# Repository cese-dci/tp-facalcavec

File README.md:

# Cargador modular de baterías industriales con acceso remoto

Repositorio perteneciente a la materia Diseño de circuitos impresos del CESE - 2021.

En el se encontrará el diseño del esquemático y PCB del TP final de la carrera.

&nbsp;

## Consideraciones de diseño del PCB

Se detallan a continuación los considerandos a tener en cuenta en el diseño y construcción del circuito impreso del cargador modular de baterías industriales.

### Dimensiones y ubicación
La placa debe adaptarse a un gabinete ya existente, por lo tanto sus medidas no deben superar los siguientes límites

Largo máximo      : 200 mm  
Ancho máximo      : 100 mm  

### Coordenadas de los agujero de montaje ( vista la placa de frente )

Agujero inferior izquierdo  : ( 0 mm, 0 mm )  
Agujero inferior derecho    : ( 184 mm, 0 mm )  
Agujero superior izquierdo  : ( 0 mm, -86 mm )  
Agujero superior derecho    : ( 184 mm, -86 mm )  

### Coordenadas del Display gráfico respecto del agujero inferior izquierdo

Ángulo inferior izquierdo   : ( 16 mm, -18.5 mm )  
Ángulo inferior derecho     : ( 102.5 mm, -18.5 mm )  
Ángulo superior izquierdo   : ( 16 mm, -72 mm )  
Ángulo superior derecho     : ( 102.5 mm, -72 mm )  

### Coordenadas del teclado respecto del agujero inferior izquierdo  
Centro botón 1    : ( 21 mm, -2 mm )  
Centro botón 2    : ( 46.7 mm, -2 mm )  
Centro botón 3    : ( 72 mm, -2 mm )  
Centro botón 4    : ( 997.5 mm, -2 mm )  

### Estándares de fabricación
Debido a la poca densidad de conexiones entre componentes el diseño se realizará en doble faz ( dos capas ).
&nbsp;
De acuerdo a la documentación aportada por el fabricantede PCB Mayer se implementará la tecnología “8MILS” donde  
&nbsp;
Diámetro de agujero: 16 mils / 0.40 mm  
Diámetro de pad o vía: 32 mils / 0.8 mm  
Ancho de traza: 8 mils / 0.20 mm  
Separación entre trazas: 7 mils / 0.18 mm  
Separación entre traza y pad: 6 mils / 0.15 mm  
Distancia de cobre a borde: 12 mils / 0.30 mm  
Altura - trazo de letras: 30 - 5  

### Componentes a utilizar  
Para el diseño de la placa se utilizarán componentes SMD para las resistencias, capacitores cerámicos y algunos circuitos integrados, mientras que el resto serán del tipo insertados (THT).  
Este criterio se debe a que la mayoría de los componentes que integran la placa se quieren adquirir en el mercado local.  
Para aprovechar el espacio disponible se colocaran componentes SMD en las dos caras del PCB.

### Método de armado
El tipo de armado y soldado de la placa se pretende hacer de forma manual

------------------------------------------------------------------------

&nbsp;

&nbsp;

<br />This work is licensed under a <a rel="license" href="http://creativecommons.org/licenses/by-nc-sa/4.0/">Creative Commons Attribution-NonCommercial-ShareAlike 4.0 International License</a>.

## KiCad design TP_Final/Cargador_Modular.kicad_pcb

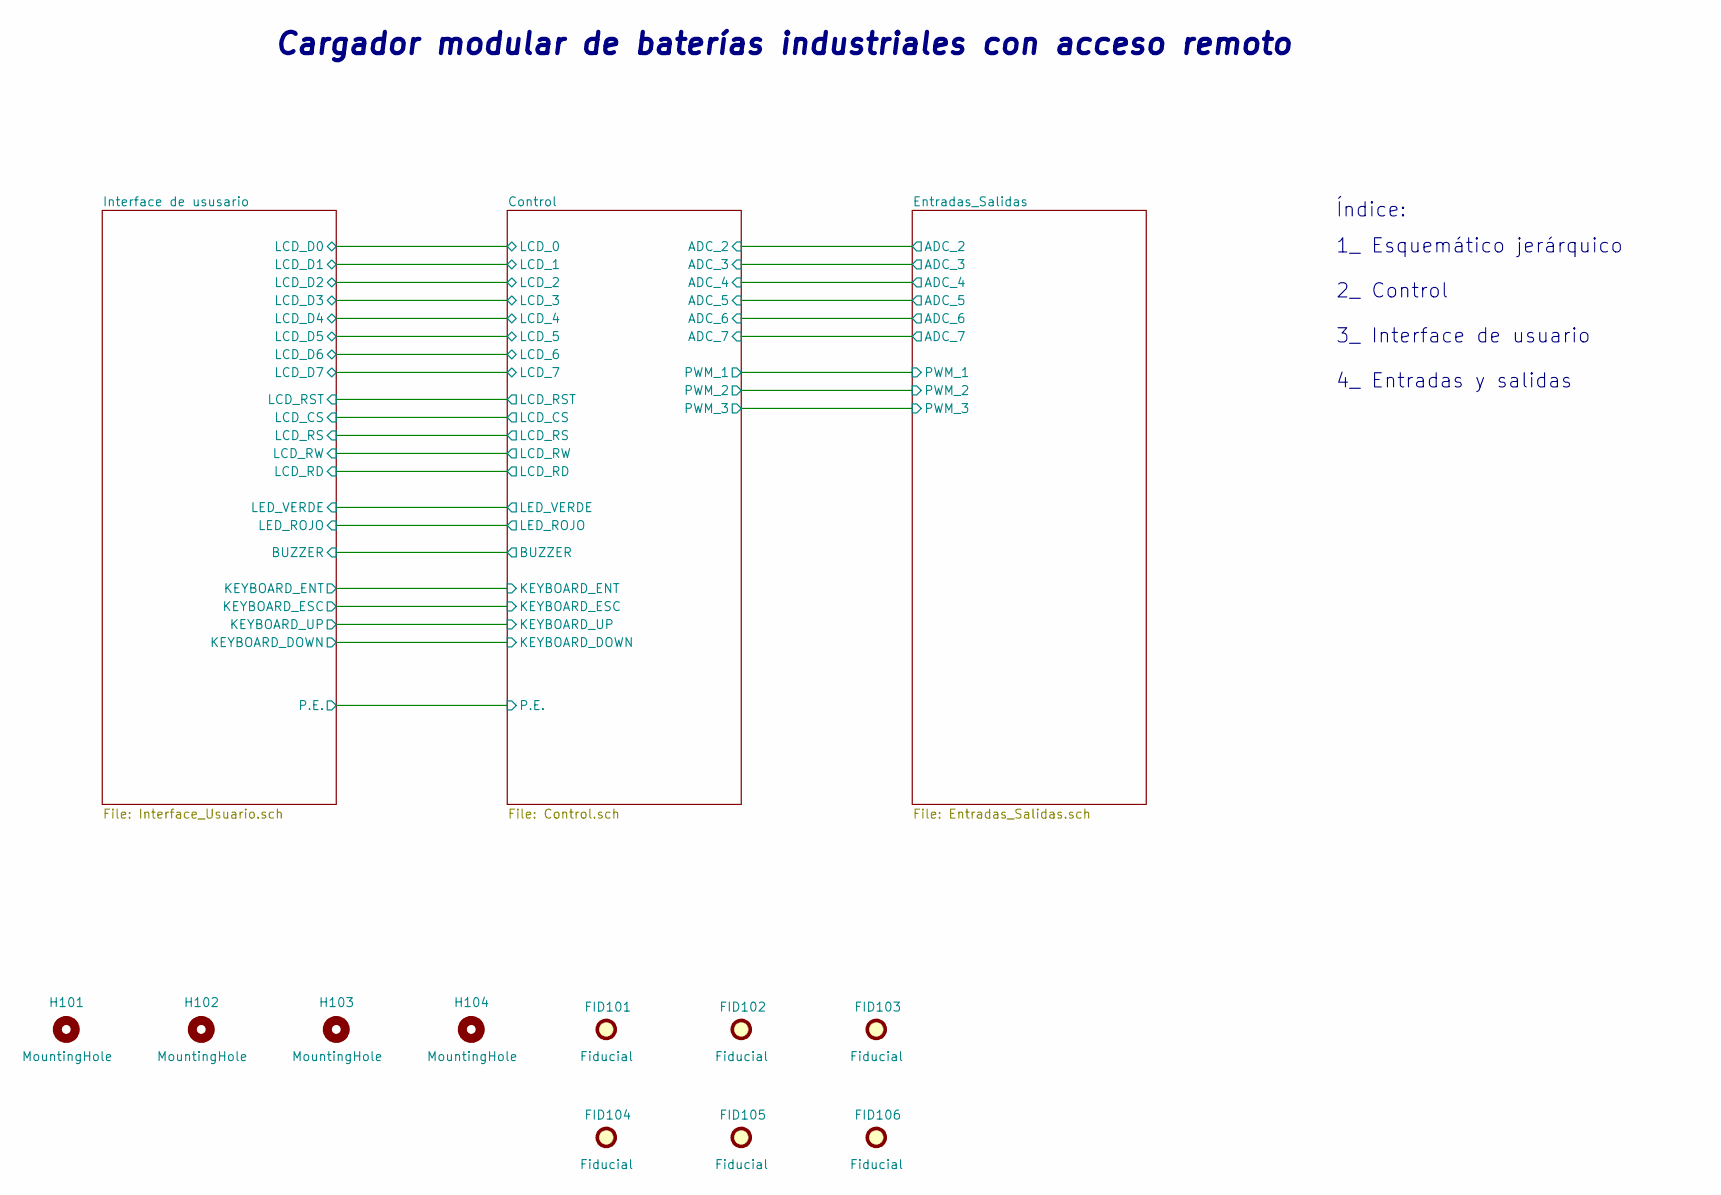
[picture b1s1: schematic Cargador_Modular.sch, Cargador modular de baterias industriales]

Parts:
FID101, FID102, FID103, FID104, FID105, FID106: Fiducial; Fiducial_0.75mm_Mask1.5mm
H101, H102, H103, H104: MountingHole; MountingHole_4.5mm_Pad

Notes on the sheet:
Cargador modular de baterías industriales con acceso remoto
4_ Entradas y salidas
3_ Interface de usuario
2_ Control
1_ Esquemático jerárquico
Índice:

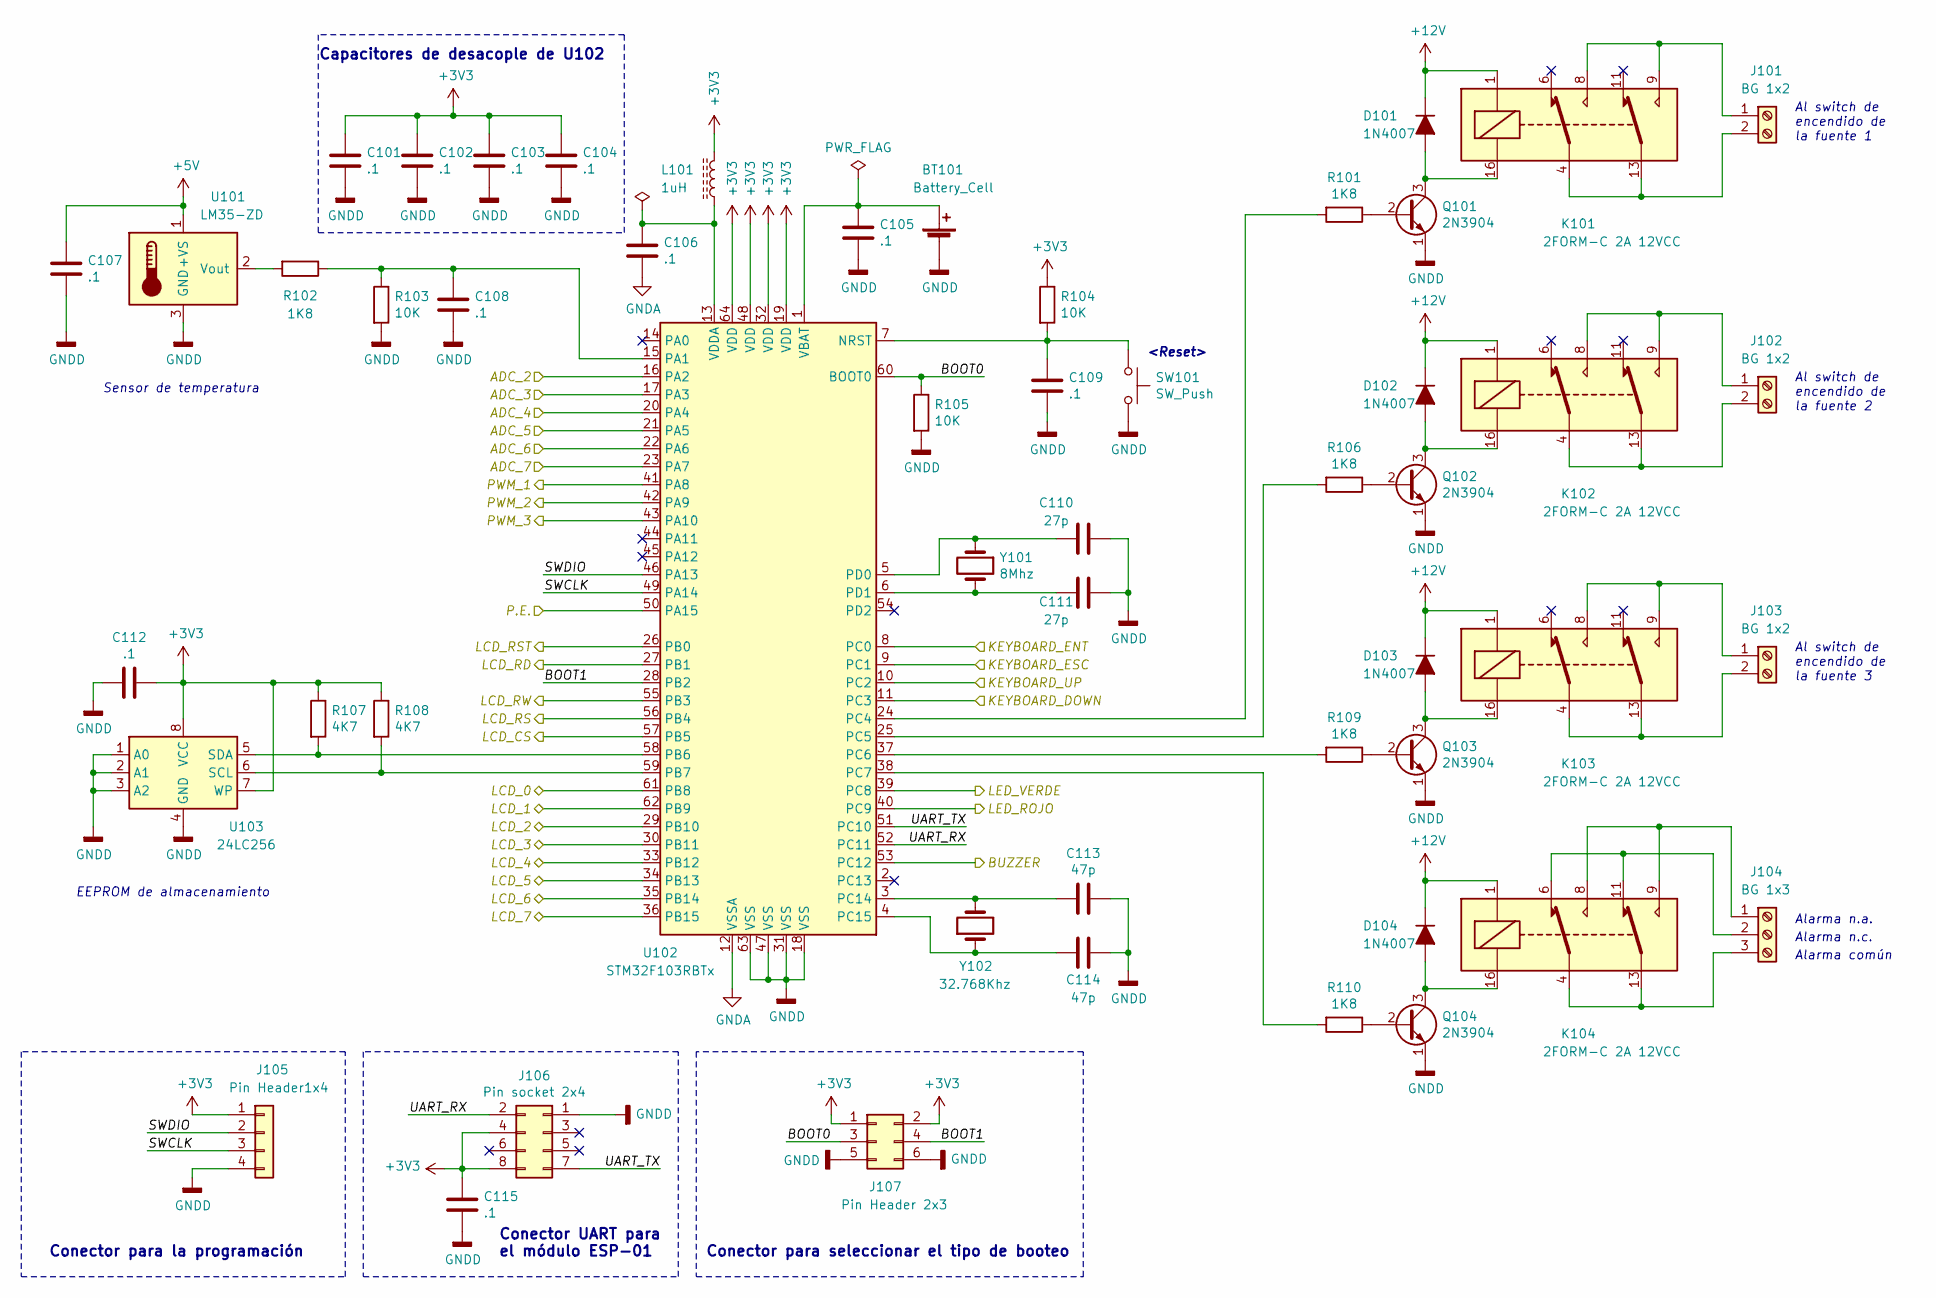
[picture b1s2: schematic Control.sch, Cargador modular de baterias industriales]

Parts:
BT101: Battery_Cell; BatteryHolder_Keystone_3034_1x20mm; Digikey part 36-2997-ND
C101, C102, C103, C104, C105, C106, C107, C108, C109, C112, C115: .1; C_0805_2012Metric
C110, C111: 27p; C_0805_2012Metric
C113, C114: 47p; C_0805_2012Metric
D101, D102, D103, D104: 1N4007; D_DO-41_SOD81_P10.16mm_Horizontal
J101, J102, J103: BG 1x2; TerminalBlock_Phoenix_PT-1,5-2-5.0-H_1x02_P5.00mm_Horizontal
J104: BG 1x3; TerminalBlock_Phoenix_PT-1,5-3-5.0-H_1x03_P5.00mm_Horizontal
J105: Pin Header1x4; PinHeader_1x04_P2.54mm_Vertical
J106: Pin socket 2x4; PinSocket_2x04_P2.54mm_Vertical
J107: Pin Header 2x3; PinHeader_2x03_P2.54mm_Vertical
K101, K102, K103, K104: 2FORM-C 2A 12VCC; Relay_DPDT_Omron_G5V-2
L101: 1uH; L_Axial_L5.3mm_D2.2mm_P7.62mm_Horizontal_Vishay_IM-1
Q101, Q102, Q103, Q104: 2N3904; TO-92_HandSolder
R101, R102, R106, R109, R110: 1K8; R_1206_3216Metric
R103, R104, R105: 10K; R_1206_3216Metric
R107, R108: 4K7; R_1206_3216Metric
SW101: SW_Push; SW_PUSH_6mm_H4.3mm
U101: LM35-ZD; TO-92_HandSolder; Digikey part 296-35151-1-ND
U102: STM32F103RBTx; LQFP-64_10x10mm_P0.5mm; Digikey part 497-6066-ND
U103: 24LC256; SOIC-8_3.9x4.9mm_P1.27mm; Digikey part 24LC256T-I/SNDKR-ND
Y101: 8Mhz; Crystal_HC49-4H_Vertical
Y102: 32.768Khz; Crystal_C26-LF_D2.1mm_L6.5mm_Horizontal_1EP_style2

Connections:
+3V3: C101.1, C102.1, C103.1, C104.1, C112.1, C115.1, J105.1, J106.4, J106.8, J107.1, J107.2, L101.2, R104.1, R107.1, R108.1, U102.19 (VDD), U102.32 (VDD), U102.48 (VDD), U102.64 (VDD), U103.7 (WP), U103.8 (VCC); also elsewhere on the board
+5V: C107.1, U101.1 (+VS); also elsewhere on the board
+12V: D101.1 (K), D102.1 (K), D103.1 (K), D104.1 (K), K101.1, K102.1, K103.1, K104.1; also elsewhere on the board
/Control/ADC_2: U102.16 (PA2); also elsewhere on the board
/Control/ADC_3: U102.17 (PA3); also elsewhere on the board
/Control/ADC_4: U102.20 (PA4); also elsewhere on the board
/Control/ADC_5: U102.21 (PA5); also elsewhere on the board
/Control/ADC_6: U102.22 (PA6); also elsewhere on the board
/Control/ADC_7: U102.23 (PA7); also elsewhere on the board
/Control/BOOT0: J107.3, R105.1, U102.60 (BOOT0)
/Control/BOOT1: J107.4, U102.28 (PB2)
/Control/BUZZER: U102.53 (PC12); also elsewhere on the board
/Control/KEYBOARD_DOWN: U102.11 (PC3); also elsewhere on the board
/Control/KEYBOARD_ENT: U102.8 (PC0); also elsewhere on the board
/Control/KEYBOARD_ESC: U102.9 (PC1); also elsewhere on the board
/Control/KEYBOARD_UP: U102.10 (PC2); also elsewhere on the board
/Control/LCD_0: U102.61 (PB8); also elsewhere on the board
/Control/LCD_1: U102.62 (PB9); also elsewhere on the board
/Control/LCD_2: U102.29 (PB10); also elsewhere on the board
/Control/LCD_3: U102.30 (PB11); also elsewhere on the board
/Control/LCD_4: U102.33 (PB12); also elsewhere on the board
/Control/LCD_5: U102.34 (PB13); also elsewhere on the board
/Control/LCD_6: U102.35 (PB14); also elsewhere on the board
/Control/LCD_7: U102.36 (PB15); also elsewhere on the board
/Control/LCD_CS: U102.57 (PB5); also elsewhere on the board
/Control/LCD_RD: U102.27 (PB1); also elsewhere on the board
/Control/LCD_RS: U102.56 (PB4); also elsewhere on the board
/Control/LCD_RST: U102.26 (PB0); also elsewhere on the board
/Control/LCD_RW: U102.55 (PB3); also elsewhere on the board
/Control/LED_ROJO: U102.40 (PC9); also elsewhere on the board
/Control/LED_VERDE: U102.39 (PC8); also elsewhere on the board
/Control/P.E.: U102.50 (PA15); also elsewhere on the board
/Control/PWM_1: U102.41 (PA8); also elsewhere on the board
/Control/PWM_2: U102.42 (PA9); also elsewhere on the board
/Control/PWM_3: U102.43 (PA10); also elsewhere on the board
/Control/SWCLK: J105.3, U102.49 (PA14)
/Control/SWDIO: J105.2, U102.46 (PA13)
/Control/UART_RX: J106.2, U102.52 (PC11)
/Control/UART_TX: J106.7, U102.51 (PC10)
GNDA: BT101.2 (-), C101.2, C102.2, C103.2, C104.2, C105.2, C106.2, C107.2, C108.2, C109.2, C110.1, C111.1, C112.2, C113.1, C114.1, C115.2, J105.4, J106.1, J107.5, J107.6, Q101.1 (E), Q102.1 (E), Q103.1 (E), Q104.1 (E), R103.2, R105.2, SW101.2, U101.3 (GND), U102.12 (VSSA), U102.18 (VSS), U102.31 (VSS), U102.47 (VSS), U102.63 (VSS), U103.1 (A0), U103.2 (A1), U103.3 (A2), U103.4 (GND); also elsewhere on the board
unnamed: BT101.1 (+), C105.1, U102.1 (VBAT)
unnamed: C106.1, L101.1, U102.13 (VDDA)
unnamed: C108.1, R102.1, R103.1, U102.15 (PA1)
unnamed: C109.1, R104.2, SW101.1, U102.7 (NRST)
unnamed: C110.2, U102.5 (PD0), Y101.1
unnamed: C111.2, U102.6 (PD1), Y101.2
unnamed: C113.2, U102.3 (PC14), Y102.2
unnamed: C114.2, U102.4 (PC15), Y102.1
unnamed: D101.2 (A), K101.16, Q101.3 (C)
unnamed: D102.2 (A), K102.16, Q102.3 (C)
unnamed: D103.2 (A), K103.16, Q103.3 (C)
unnamed: D104.2 (A), K104.16, Q104.3 (C)
unnamed: J101.1, K101.8, K101.9
unnamed: J101.2, K101.4, K101.13
unnamed: J102.1, K102.8, K102.9
unnamed: J102.2, K102.4, K102.13
unnamed: J103.1, K103.8, K103.9
unnamed: J103.2, K103.4, K103.13
unnamed: J104.1, K104.8, K104.9
unnamed: J104.2, K104.6, K104.11
unnamed: J104.3, K104.4, K104.13
unnamed: Q101.2 (B), R101.1
unnamed: Q102.2 (B), R106.1
unnamed: Q103.2 (B), R109.1
unnamed: Q104.2 (B), R110.1
unnamed: R101.2, U102.24 (PC4)
unnamed: R102.2, U101.2 (Vout)
unnamed: R106.2, U102.25 (PC5)
unnamed: R107.2, U102.58 (PB6), U103.5 (SDA)
unnamed: R108.2, U102.59 (PB7), U103.6 (SCL)
unnamed: R109.2, U102.37 (PC6)
unnamed: R110.2, U102.38 (PC7)

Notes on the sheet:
Conector para la programación
Conector UART para el módulo ESP-01
Conector para seleccionar el tipo de booteo
Al switch de encendido de la fuente 1
Al switch de encendido de la fuente 2
Al switch de encendido de la fuente 3
Alarma común
Alarma n.a.
Alarma n.c.
Sensor de temperatura
EEPROM de almacenamiento
<Reset>
Capacitores de desacople de U102

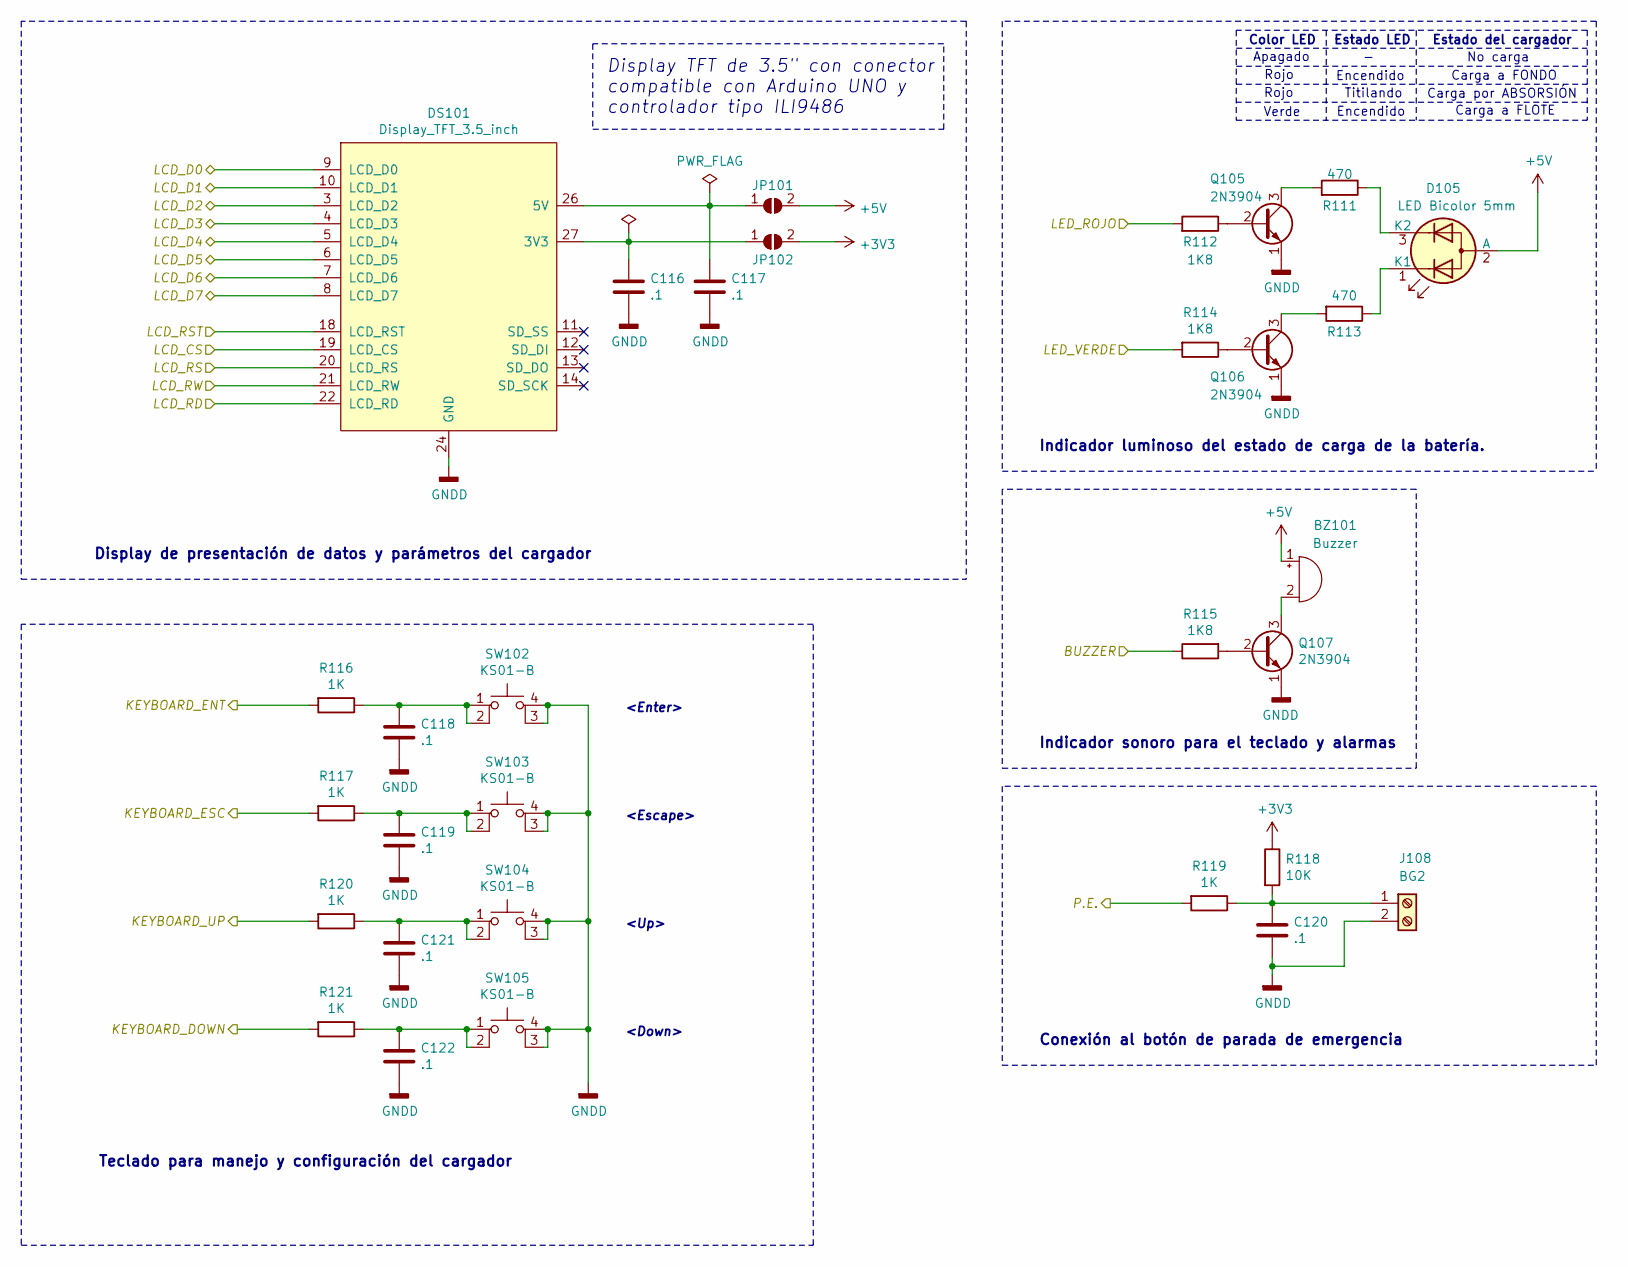
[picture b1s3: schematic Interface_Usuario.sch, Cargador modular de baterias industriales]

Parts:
BZ101: Buzzer; Buzzer_12x9.5RM7.6
C116, C117, C118, C119, C120, C121, C122: .1; C_0805_2012Metric
D105: LED Bicolor 5mm; LED_D5.0mm-3; Digikey part 1080-1110-ND
DS101: Display_TFT_3.5_inch; Part # N/A
J108: BG2; TerminalBlock_Phoenix_PT-1,5-2-5.0-H_1x02_P5.00mm_Horizontal
JP101, JP102: SolderJumper_2_Open; SolderJumper-2_P1.3mm_Open_RoundedPad1.0x1.5mm
Q105, Q106, Q107: 2N3904; TO-92_HandSolder
R111, R113: 470; R_1206_3216Metric
R112, R114, R115: 1K8; R_1206_3216Metric
R116, R117, R119, R120, R121: 1K; R_1206_3216Metric
R118: 10K; R_1206_3216Metric
SW102, SW103, SW104, SW105: KS01-B; Push_E-Switch_KS01Q01

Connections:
+3V3: JP102.2 (B), R118.1; also elsewhere on the board
+5V: BZ101.1 (-), D105.2 (A), JP101.2 (B); also elsewhere on the board
/Control/BUZZER: R115.1; also elsewhere on the board
/Control/KEYBOARD_DOWN: R121.2; also elsewhere on the board
/Control/KEYBOARD_ENT: R116.2; also elsewhere on the board
/Control/KEYBOARD_ESC: R117.2; also elsewhere on the board
/Control/KEYBOARD_UP: R120.2; also elsewhere on the board
/Control/LCD_0: DS101.9 (LCD_D0); also elsewhere on the board
/Control/LCD_1: DS101.10 (LCD_D1); also elsewhere on the board
/Control/LCD_2: DS101.3 (LCD_D2); also elsewhere on the board
/Control/LCD_3: DS101.4 (LCD_D3); also elsewhere on the board
/Control/LCD_4: DS101.5 (LCD_D4); also elsewhere on the board
/Control/LCD_5: DS101.6 (LCD_D5); also elsewhere on the board
/Control/LCD_6: DS101.7 (LCD_D6); also elsewhere on the board
/Control/LCD_7: DS101.8 (LCD_D7); also elsewhere on the board
/Control/LCD_CS: DS101.19 (LCD_CS); also elsewhere on the board
/Control/LCD_RD: DS101.22 (LCD_RD); also elsewhere on the board
/Control/LCD_RS: DS101.20 (LCD_RS); also elsewhere on the board
/Control/LCD_RST: DS101.18 (LCD_RST); also elsewhere on the board
/Control/LCD_RW: DS101.21 (LCD_RW); also elsewhere on the board
/Control/LED_ROJO: R112.2; also elsewhere on the board
/Control/LED_VERDE: R114.2; also elsewhere on the board
/Control/P.E.: R119.2; also elsewhere on the board
GNDA: C116.2, C117.2, C118.2, C119.2, C120.2, C121.2, C122.2, DS101.24 (GND), J108.2, Q105.1 (E), Q106.1 (E), Q107.1 (E), SW102.3 (K), SW102.4 (A), SW103.3 (K), SW103.4 (A), SW104.3 (K), SW104.4 (A), SW105.3 (K), SW105.4 (A); also elsewhere on the board
unnamed: BZ101.2 (+), Q107.3 (C)
unnamed: C116.1, DS101.27 (3V3), JP102.1 (A)
unnamed: C117.1, DS101.26 (5V), JP101.1 (A)
unnamed: C118.1, R116.1, SW102.1, SW102.2
unnamed: C119.1, R117.1, SW103.1, SW103.2
unnamed: C120.1, J108.1, R118.2, R119.1
unnamed: C121.1, R120.1, SW104.1, SW104.2
unnamed: C122.1, R121.1, SW105.1, SW105.2
unnamed: D105.1 (K1), R113.1
unnamed: D105.3 (K2), R111.1
unnamed: Q105.2 (B), R112.1
unnamed: Q105.3 (C), R111.2
unnamed: Q106.2 (B), R114.1
unnamed: Q106.3 (C), R113.2
unnamed: Q107.2 (B), R115.2

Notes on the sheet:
Indicador luminoso del estado de carga de la batería.
Indicador sonoro para el teclado y alarmas
Conexión al botón de parada de emergencia
Color LED
Estado LED
Estado del cargador
Rojo
Apagado
No carga
Encendido
Carga a FONDO
Titilando
Carga por ABSORSIÓN
Verde
Carga a FLOTE
<Down>
<Up>
<Escape>
<Enter>
Teclado para manejo y configuración del cargador
Display de presentación de datos y parámetros del cargador
Display TFT de 3.5" con conector compatible con Arduino UNO y controlador tipo ILI9486

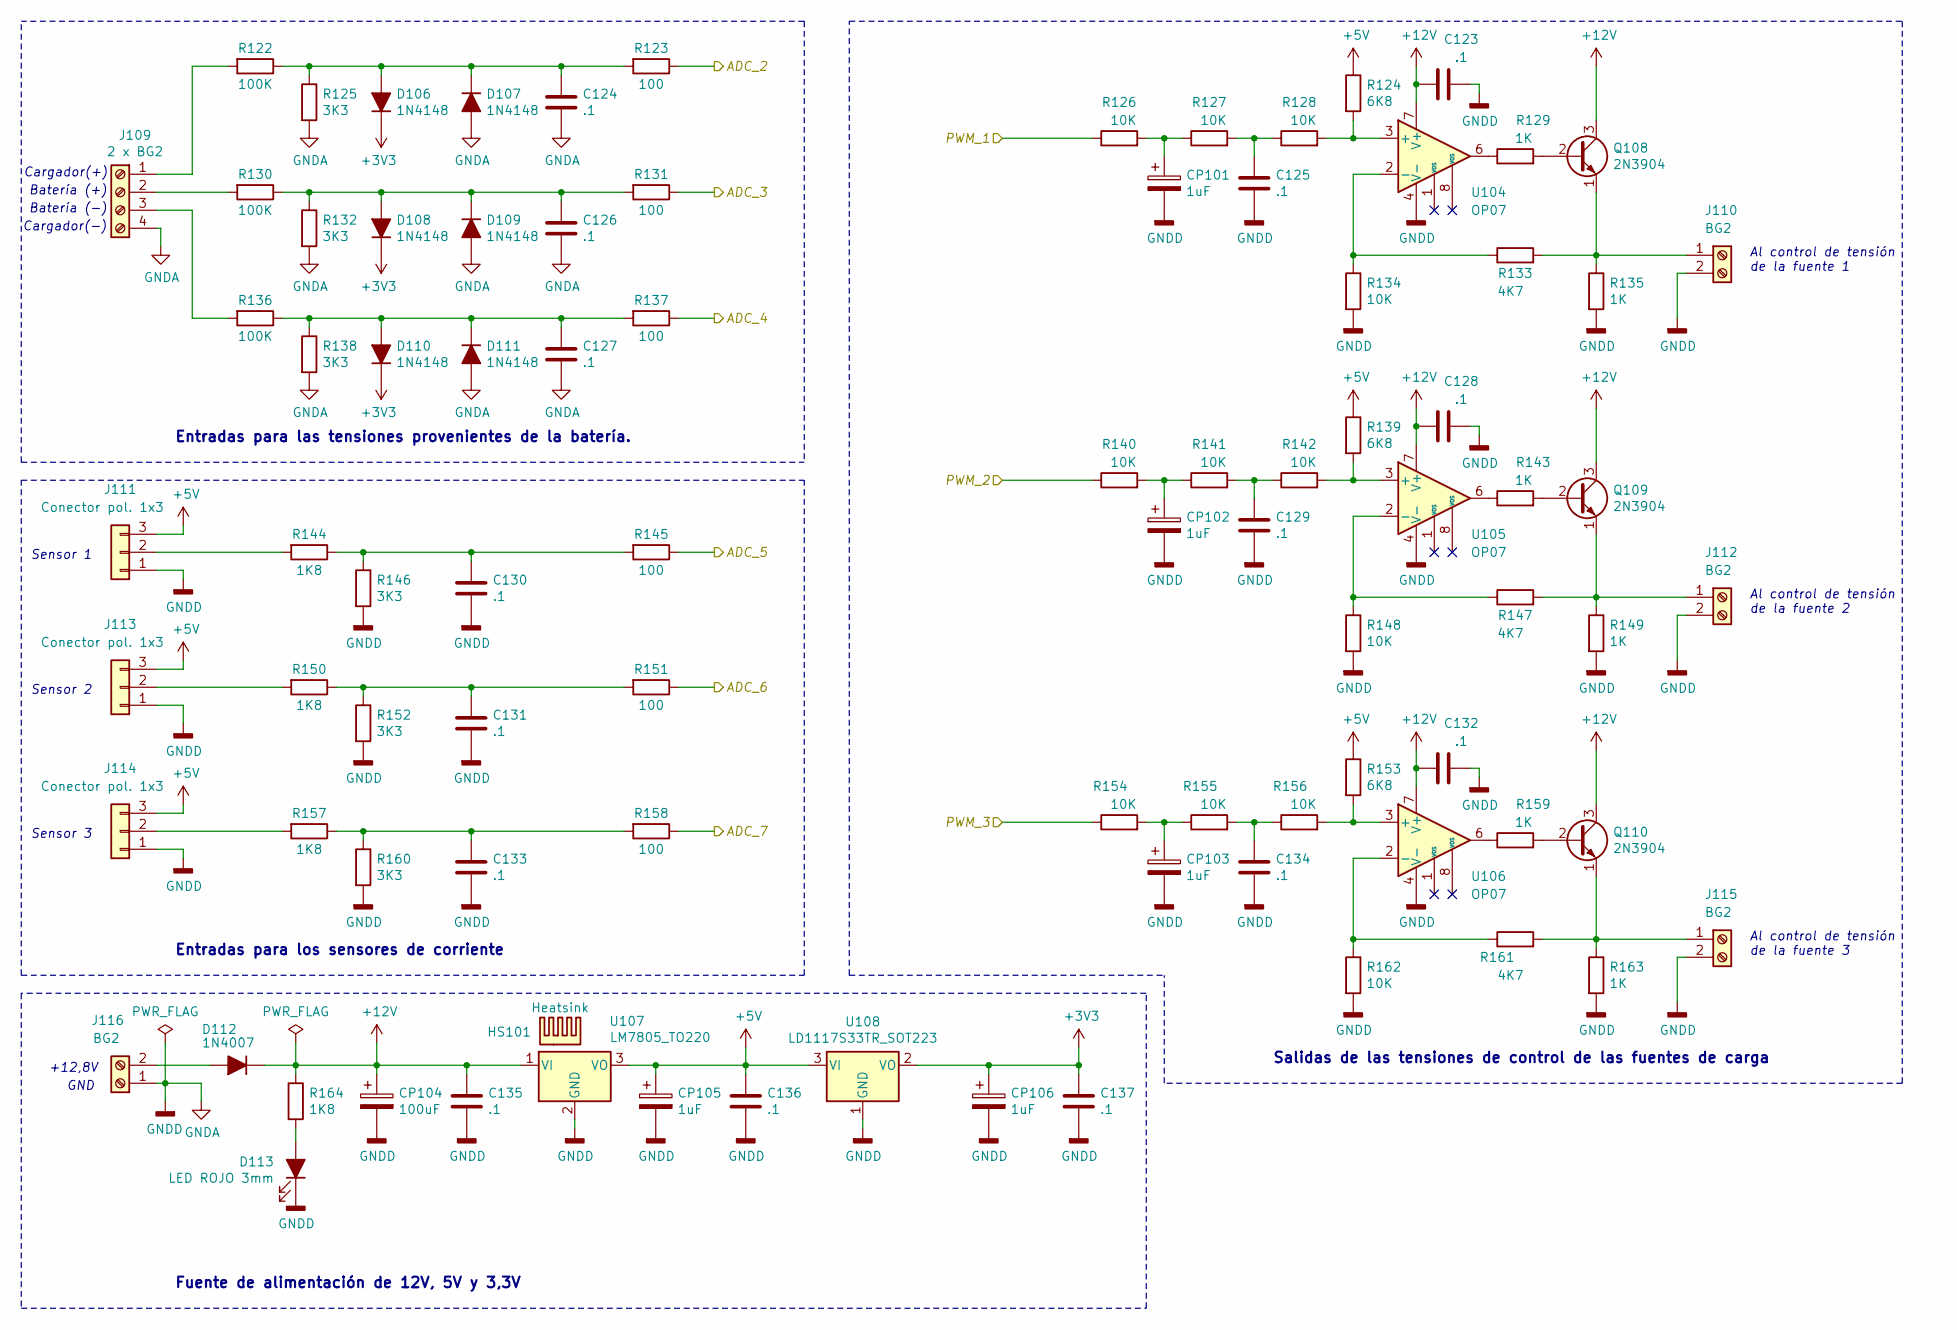
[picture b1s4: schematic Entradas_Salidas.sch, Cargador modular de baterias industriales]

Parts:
C123, C124, C125, C126, C127, C128, C129, C130, C131, C132, C133, C134, C135, C136, C137: .1; C_0805_2012Metric
CP101, CP102, CP103, CP105, CP106: 1uF; CP_Radial_D5.0mm_P2.50mm
CP104: 100uF; CP_Radial_D6.3mm_P2.50mm
D106, D107, D108, D109, D110, D111: 1N4148; D_A-405_P7.62mm_Horizontal
D112: 1N4007; D_DO-41_SOD81_P10.16mm_Horizontal
D113: LED ROJO 3mm; LED_D3.0mm
HS101: Heatsink; Heatsink_Aavid-TV5G_TO220_Horizontal
J109: 2 x BG2; TerminalBlock_Phoenix_PT-1,5-4-5.0-H_1x04_P5.00mm_Horizontal
J110, J112, J115, J116: BG2; TerminalBlock_Phoenix_PT-1,5-2-5.0-H_1x02_P5.00mm_Horizontal
J111, J113, J114: Conector pol. 1x3; JST_EH_B3B-EH-A_1x03_P2.50mm_Vertical
Q108, Q109, Q110: 2N3904; TO-92_HandSolder
R122, R130, R136: 100K; R_1206_3216Metric
R123, R131, R137, R145, R151, R158: 100; R_1206_3216Metric
R124, R139, R153: 6K8; R_1206_3216Metric
R125, R132, R138, R146, R152, R160: 3K3; R_1206_3216Metric
R126, R127, R128, R134, R140, R141, R142, R148, R154, R155, R156, R162: 10K; R_1206_3216Metric
R129, R135, R143, R149, R159, R163: 1K; R_1206_3216Metric
R133, R147, R161: 4K7; R_1206_3216Metric
R144, R150, R157, R164: 1K8; R_1206_3216Metric
U104, U105: OP07; DIP-8_W7.62mm_LongPads
U106: OP07; DIP-8_W7.62mm_LongPads; Digikey part OP07DNZ-ND
U107: LM7805_TO220; TO-220-3_Horizontal_TabDown; Digikey part MC7805ACTGOS-ND
U108: LD1117S33TR_SOT223; SOT-223-3_TabPin2; Digikey part 497-1242-1-ND

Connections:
+3V3: C137.1, CP106.1, D106.1 (K), D108.1 (K), D110.1 (K), U108.2 (VO); also elsewhere on the board
+5V: C136.1, CP105.1, J111.3, J113.3, J114.3, R124.1, R139.1, R153.1, U107.3 (VO), U108.3 (VI); also elsewhere on the board
+12V: C123.2, C128.2, C132.2, C135.1, CP104.1, D112.1 (K), Q108.3 (C), Q109.3 (C), Q110.3 (C), R164.1, U104.7 (V+), U105.7 (V+), U106.7 (V+), U107.1 (VI); also elsewhere on the board
/Control/ADC_2: R123.1; also elsewhere on the board
/Control/ADC_3: R131.1; also elsewhere on the board
/Control/ADC_4: R137.1; also elsewhere on the board
/Control/ADC_5: R145.1; also elsewhere on the board
/Control/ADC_6: R151.1; also elsewhere on the board
/Control/ADC_7: R158.1; also elsewhere on the board
/Control/PWM_1: R126.1; also elsewhere on the board
/Control/PWM_2: R140.1; also elsewhere on the board
/Control/PWM_3: R154.1; also elsewhere on the board
GNDA: C123.1, C124.2, C125.2, C126.2, C127.2, C128.1, C129.2, C130.2, C131.2, C132.1, C133.2, C134.2, C135.2, C136.2, C137.2, CP101.2, CP102.2, CP103.2, CP104.2, CP105.2, CP106.2, D107.2 (A), D109.2 (A), D111.2 (A), D113.1 (K), J109.4, J110.2, J111.1, J112.2, J113.1, J114.1, J115.2, J116.1, R125.2, R132.2, R134.2, R135.2, R138.2, R146.2, R148.2, R149.2, R152.2, R160.2, R162.2, R163.2, U104.4 (V-), U105.4 (V-), U106.4 (V-), U107.2 (GND), U108.1 (GND); also elsewhere on the board
unnamed: C124.1, D106.2 (A), D107.1 (K), R122.1, R123.2, R125.1
unnamed: C125.1, R127.2, R128.1
unnamed: C126.1, D108.2 (A), D109.1 (K), R130.1, R131.2, R132.1
unnamed: C127.1, D110.2 (A), D111.1 (K), R136.1, R137.2, R138.1
unnamed: C129.1, R141.2, R142.1
unnamed: C130.1, R144.1, R145.2, R146.1
unnamed: C131.1, R150.1, R151.2, R152.1
unnamed: C133.1, R157.1, R158.2, R160.1
unnamed: C134.1, R155.2, R156.1
unnamed: CP101.1, R126.2, R127.1
unnamed: CP102.1, R140.2, R141.1
unnamed: CP103.1, R154.2, R155.1
unnamed: D112.2 (A), J116.2
unnamed: D113.2 (A), R164.2
unnamed: J109.1, R122.2
unnamed: J109.2, R130.2
unnamed: J109.3, R136.2
unnamed: J110.1, Q108.1 (E), R133.2, R135.1
unnamed: J111.2, R144.2
unnamed: J112.1, Q109.1 (E), R147.2, R149.1
unnamed: J113.2, R150.2
unnamed: J114.2, R157.2
unnamed: J115.1, Q110.1 (E), R161.2, R163.1
unnamed: Q108.2 (B), R129.2
unnamed: Q109.2 (B), R143.2
unnamed: Q110.2 (B), R159.2
unnamed: R124.2, R128.2, U104.3 (+)
unnamed: R129.1, U104.6
unnamed: R133.1, R134.1, U104.2 (-)
unnamed: R139.2, R142.2, U105.3 (+)
unnamed: R143.1, U105.6
unnamed: R147.1, R148.1, U105.2 (-)
unnamed: R153.2, R156.2, U106.3 (+)
unnamed: R159.1, U106.6
unnamed: R161.1, R162.1, U106.2 (-)

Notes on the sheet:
Fuente de alimentación de 12V, 5V y 3,3V
Entradas para los sensores de corriente
Entradas para las tensiones provenientes de la batería.
Salidas de las tensiones de control de las fuentes de carga
Batería (+)
Cargador(+)
Batería (-)
+12,8V
GND
Al control de tensión de la fuente 2
Al control de tensión de la fuente 3
Sensor 1
Sensor 2
Sensor 3
Cargador(-)
Al control de tensión de la fuente 1

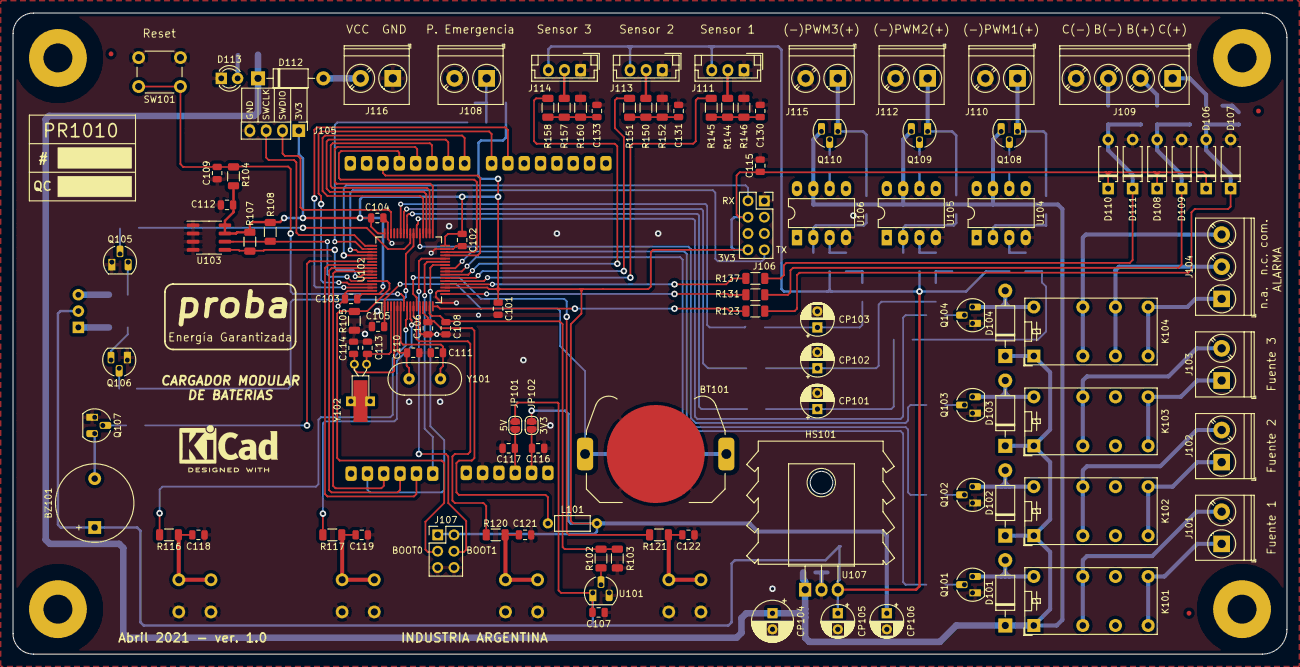
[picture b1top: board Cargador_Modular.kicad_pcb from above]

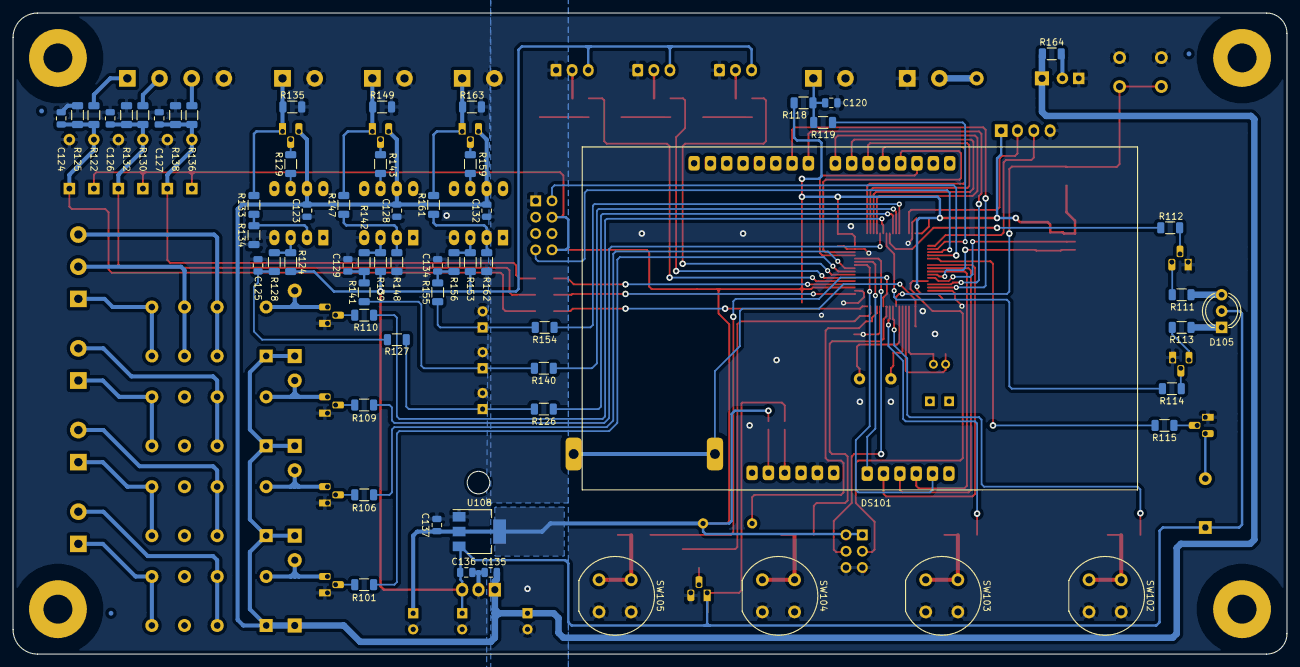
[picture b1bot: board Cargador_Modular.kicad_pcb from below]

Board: 2 copper layers, 198.1 x 99.7 mm, 182 parts (65 on the bottom side), 122 nets.

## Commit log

2021-03-21 confeccion esquematico
2021-03-26 Se completa rotulo
2021-03-26 Revisión y agregado de datasheet
2021-03-28 se agregan descripciones a componentes del esquemático
2021-04-02 Se avanza con el ruteo del PCB
2021-04-10 Agrego agujeros de montaje y fiduciales al esquematico
2021-04-10 se corrigen errores detectados con DRC
2021-04-15 Se cambio huella del portapilas y se completo el relleno de cobre
2021-04-15 se completa el relleno de cobre
2021-04-15 Update consideraciones de diseño
2021-04-17 Se finaliza el diseño del PCB
2021-04-17 Se agrga el modelo 3D
2021-04-21 Correccion power flag y digikey part
2021-04-21 Correccion bordes, fabricante y licencia
